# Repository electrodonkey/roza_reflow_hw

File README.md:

# roza_reflow_hw
Reflow controller

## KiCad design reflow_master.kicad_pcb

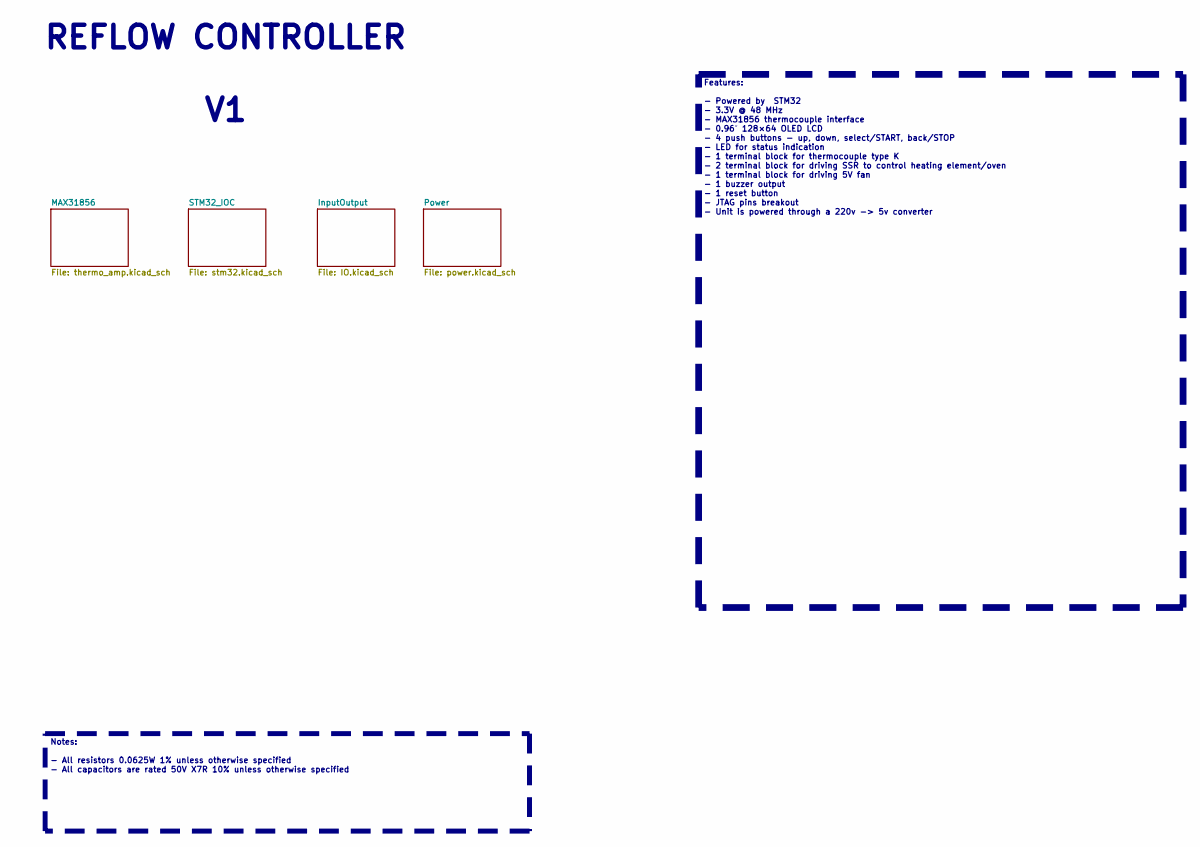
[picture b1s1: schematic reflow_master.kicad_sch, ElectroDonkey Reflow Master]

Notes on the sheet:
Features: - Powered by STM32 - 3.3V @ 48 MHz - MAX31856 thermocouple interface - 0.96″ 128×64 OLED LCD - 4 push buttons - up, down, select/START, back/STOP - LED for status indication - 1 terminal block for thermocouple type K - 2 terminal block for driving SSR to control heating element/oven - 1 t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
Notes: - All resistors 0.0625W 1% unless otherwise specified - All capacitors are rated 50V X7R 10% unless otherwise specified
REFLOW CONTROLLER ${REVISION}

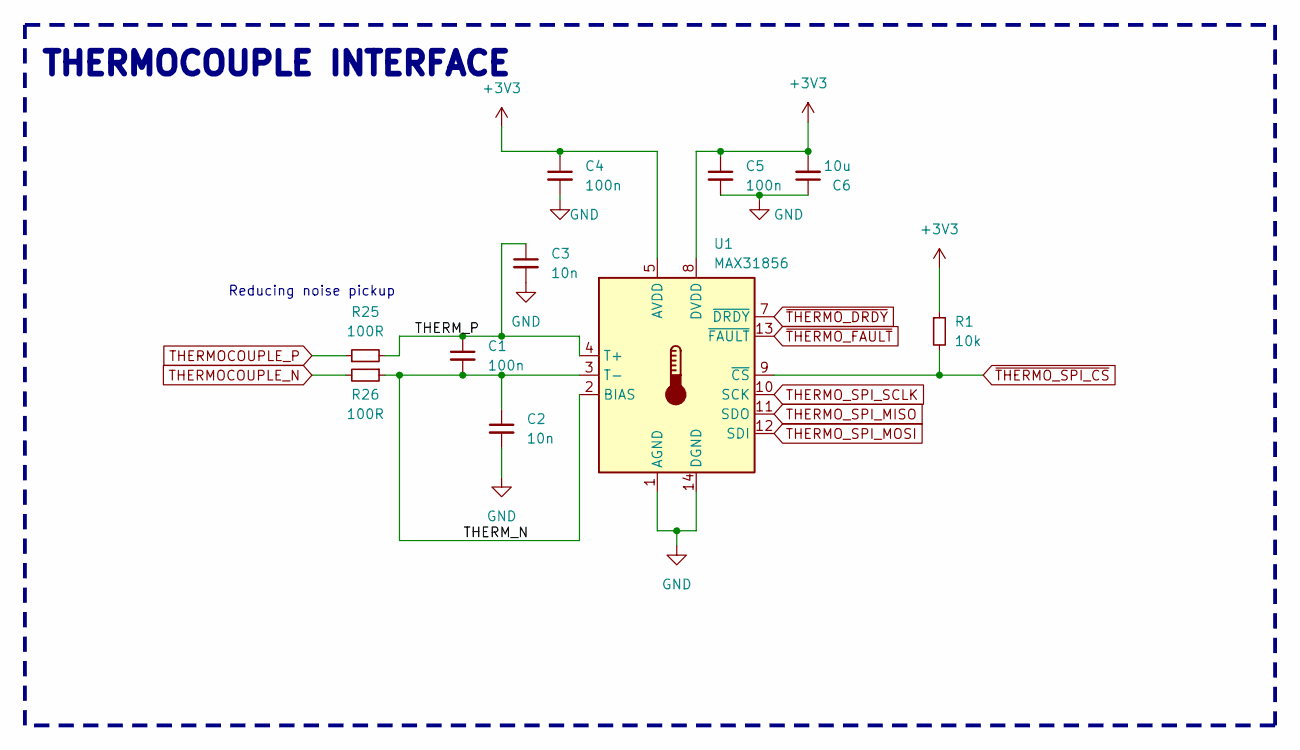
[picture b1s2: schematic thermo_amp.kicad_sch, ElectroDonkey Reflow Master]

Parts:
C1, C4, C5: 100n; C_0603_1608Metric_Pad1.08x0.95mm_HandSolder
C2, C3: 10n; C_0603_1608Metric_Pad1.08x0.95mm_HandSolder
C6: 10u; C_0603_1608Metric_Pad1.08x0.95mm_HandSolder
R1: 10k; R_0603_1608Metric_Pad0.98x0.95mm_HandSolder
R25, R26: 100R; R_0603_1608Metric_Pad0.98x0.95mm_HandSolder
U1: MAX31856; TSSOP-14_4.4x5mm_P0.65mm

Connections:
+3V3: C4.1, C5.1, C6.2, R1.1, U1.5 (AVDD), U1.8 (DVDD); also elsewhere on the board
/MAX31856/THERM_N: C1.2, C2.1, R26.1, U1.2 (BIAS), U1.3 (T-)
/MAX31856/THERM_P: C1.1, C3.1, R25.2, U1.4 (T+)
GND: C2.2, C3.2, C4.2, C5.2, C6.1, U1.1 (AGND), U1.14 (DGND); also elsewhere on the board
THERMOCOUPLE_N: R26.2; also elsewhere on the board
THERMOCOUPLE_P: R25.1; also elsewhere on the board
THERMO_SPI_MISO: U1.11 (SDO); also elsewhere on the board
THERMO_SPI_MOSI: U1.12 (SDI); also elsewhere on the board
THERMO_SPI_SCLK: U1.10 (SCK); also elsewhere on the board
~THERMO_DRDY: U1.7 (~DRDY); also elsewhere on the board
~THERMO_FAULT: U1.13 (~FAULT); also elsewhere on the board
~THERMO_SPI_CS: R1.2, U1.9 (~CS); also elsewhere on the board

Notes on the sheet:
Reducing noise pickup
THERMOCOUPLE INTERFACE

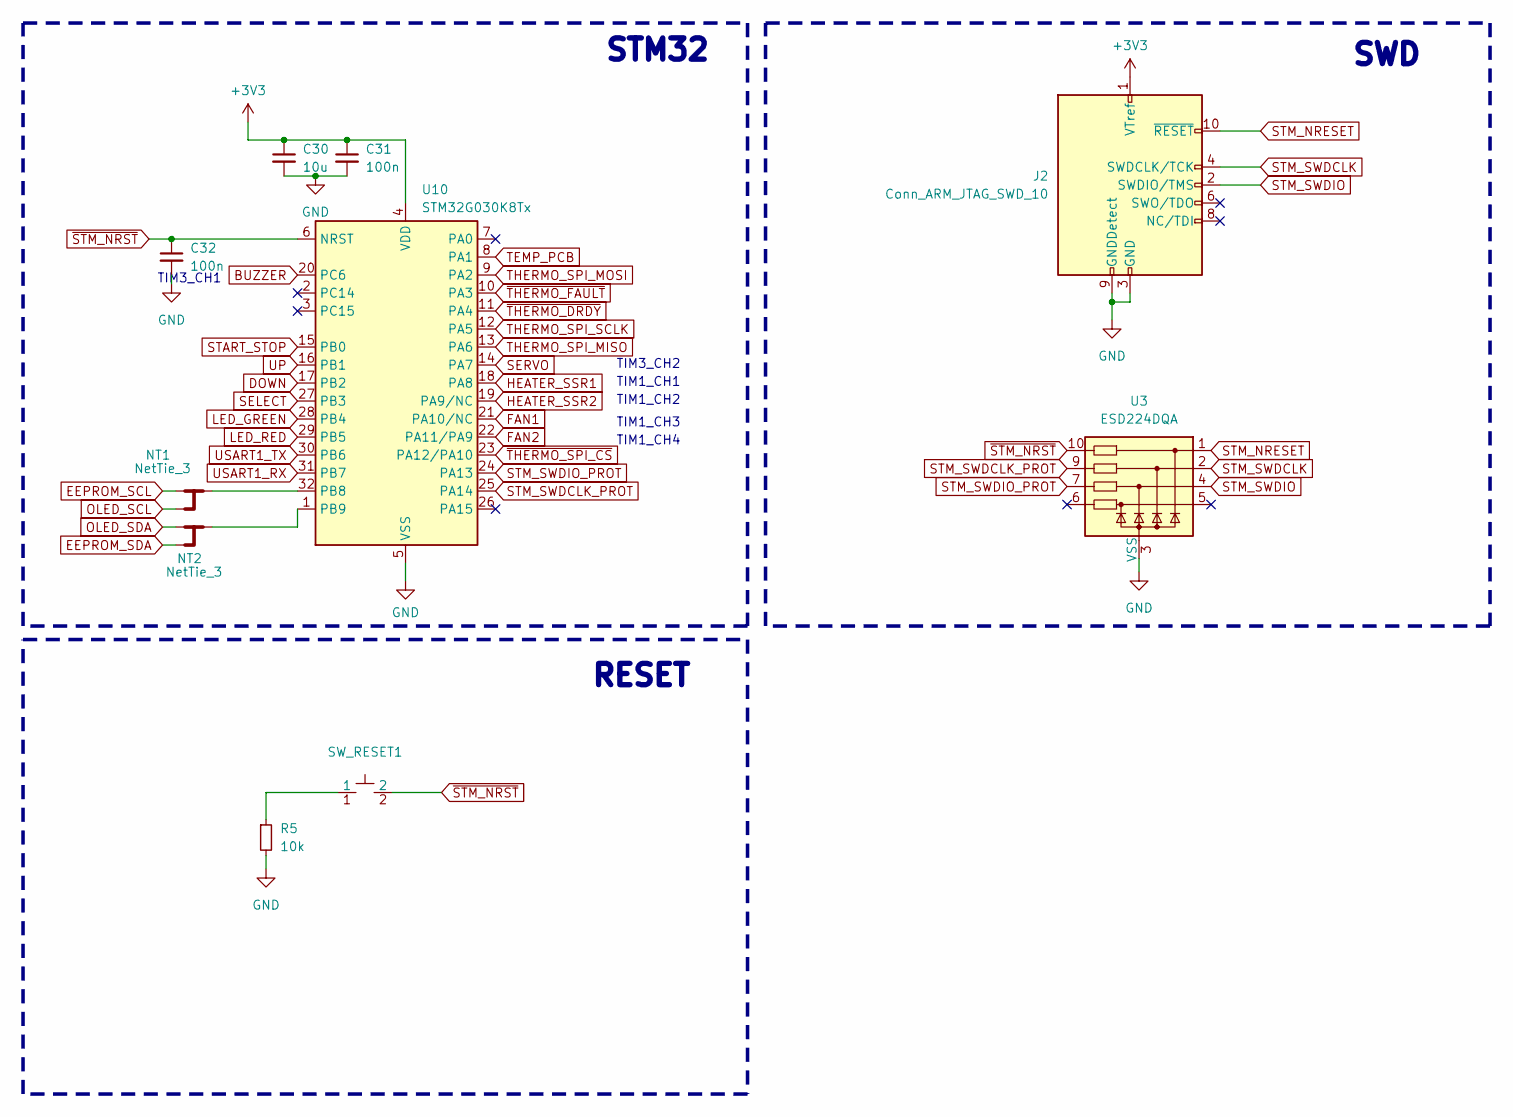
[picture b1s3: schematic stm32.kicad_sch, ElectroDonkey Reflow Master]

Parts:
C30: 10u; C_0603_1608Metric_Pad1.08x0.95mm_HandSolder
C31, C32: 100n; C_0603_1608Metric_Pad1.08x0.95mm_HandSolder
J2: Conn_ARM_JTAG_SWD_10; PinHeader_2x05_P1.27mm_Vertical
NT1, NT2: NetTie_3; NetTie-3_SMD_Pad0.5mm
R5: 10k; R_0603_1608Metric_Pad0.98x0.95mm_HandSolder
SW_RESET1: TL1017AABF160QG
U3: ESD224DQA; Diodes_UDFN-10_1.0x2.5mm_P0.5mm
U10: STM32G030K8Tx; LQFP-32_7x7mm_P0.8mm

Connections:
+3V3: C30.1, C31.1, J2.1 (VTref), U10.4 (VDD); also elsewhere on the board
BUZZER: U10.20 (PC6); also elsewhere on the board
DOWN: U10.17 (PB2); also elsewhere on the board
EEPROM_SCL: NT1.1; also elsewhere on the board
EEPROM_SDA: NT2.3; also elsewhere on the board
FAN1: U10.21 (PA10/NC); also elsewhere on the board
FAN2: U10.22 (PA11/PA9); also elsewhere on the board
GND: C30.2, C31.2, C32.2, J2.3 (GND), J2.5 (GND), J2.9 (GNDDetect), R5.2, U3.3 (VSS), U3.8 (VSS), U10.5 (VSS); also elsewhere on the board
HEATER_SSR1: U10.18 (PA8); also elsewhere on the board
HEATER_SSR2: U10.19 (PA9/NC); also elsewhere on the board
LED_GREEN: U10.28 (PB4); also elsewhere on the board
LED_RED: U10.29 (PB5); also elsewhere on the board
unnamed: R5.1, SW_RESET1.1
unnamed: NT1.2, U10.32 (PB8)
unnamed: NT2.2, U10.1 (PB9)
OLED_SCL: NT1.3; also elsewhere on the board
OLED_SDA: NT2.1; also elsewhere on the board
SELECT: U10.27 (PB3); also elsewhere on the board
SERVO: U10.14 (PA7); also elsewhere on the board
START_STOP: U10.15 (PB0); also elsewhere on the board
STM_NRESET: J2.10 (~RESET), U3.1
STM_SWDCLK: J2.4 (SWDCLK/TCK), U3.2
STM_SWDCLK_PROT: U3.9, U10.25 (PA14)
STM_SWDIO: J2.2 (SWDIO/TMS), U3.4
STM_SWDIO_PROT: U3.7, U10.24 (PA13)
TEMP_PCB: U10.8 (PA1); also elsewhere on the board
THERMO_SPI_MISO: U10.13 (PA6); also elsewhere on the board
THERMO_SPI_MOSI: U10.9 (PA2); also elsewhere on the board
THERMO_SPI_SCLK: U10.12 (PA5); also elsewhere on the board
UP: U10.16 (PB1); also elsewhere on the board
USART1_RX: U10.31 (PB7); also elsewhere on the board
USART1_TX: U10.30 (PB6); also elsewhere on the board
~STM_NRST: C32.1, SW_RESET1.2, U3.10, U10.6 (NRST)
~THERMO_DRDY: U10.11 (PA4); also elsewhere on the board
~THERMO_FAULT: U10.10 (PA3); also elsewhere on the board
~THERMO_SPI_CS: U10.23 (PA12/PA10); also elsewhere on the board

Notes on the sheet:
TIM1_CH2
TIM3_CH1
STM32
RESET
TIM1_CH3
TIM3_CH2
SWD
TIM1_CH4
TIM1_CH1

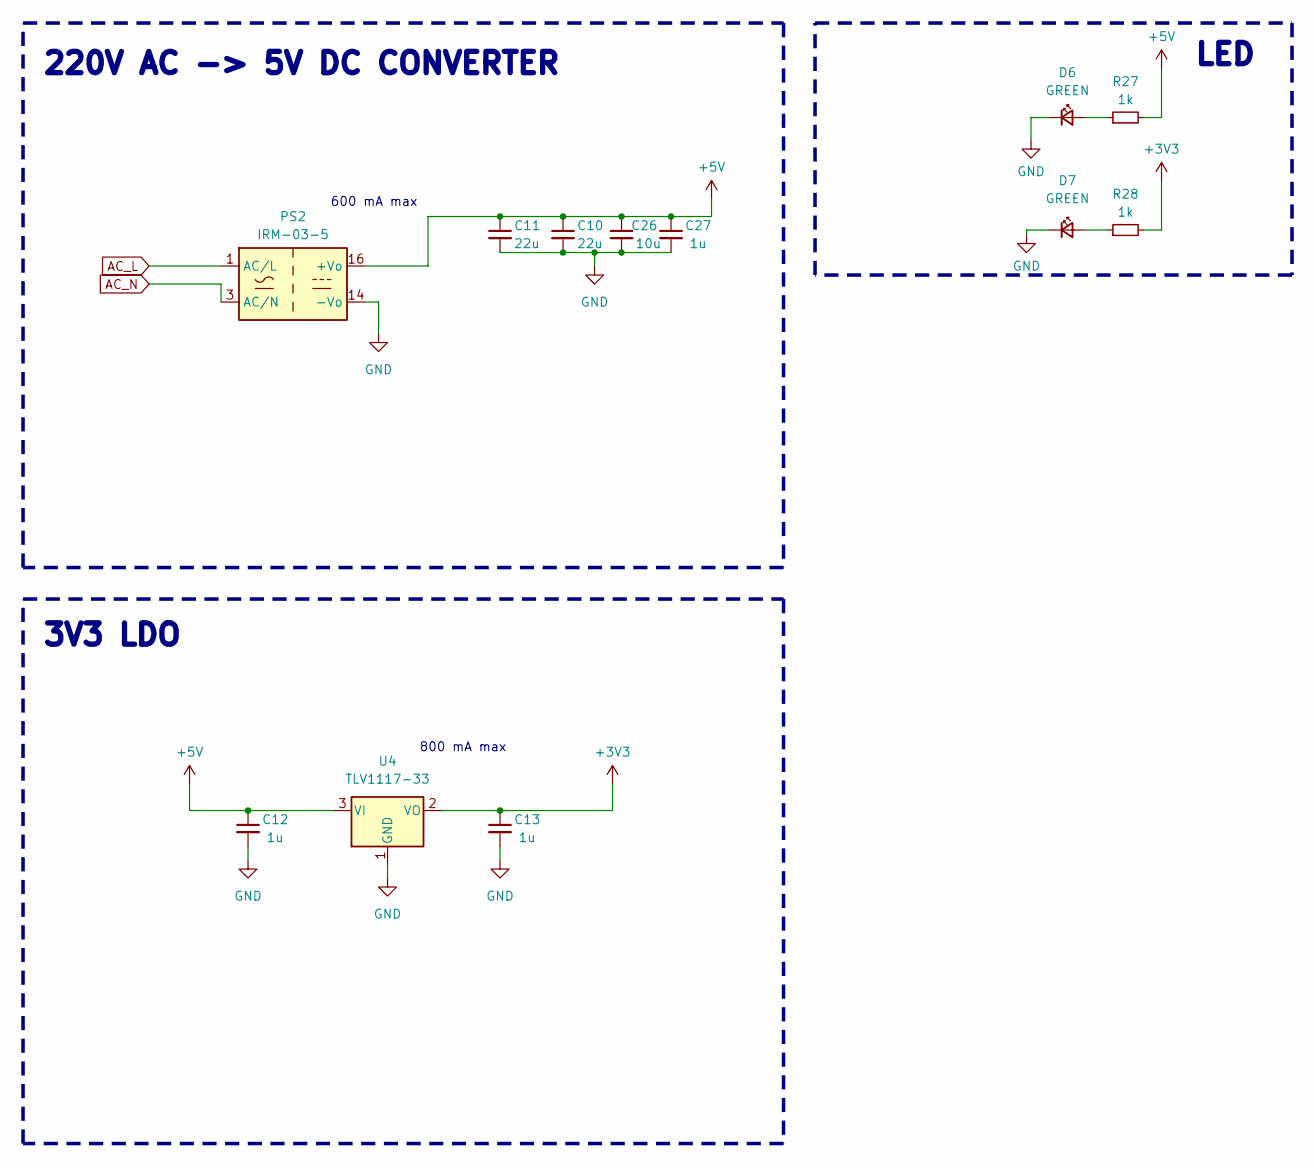
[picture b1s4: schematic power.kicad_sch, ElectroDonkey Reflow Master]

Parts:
C10, C11: 22u; C_1210_3225Metric_Pad1.33x2.70mm_HandSolder
C12, C13, C27: 1u; C_1210_3225Metric_Pad1.33x2.70mm_HandSolder
C26: 10u; C_1210_3225Metric_Pad1.33x2.70mm_HandSolder
D6, D7: GREEN; LED_0603_1608Metric_Pad1.05x0.95mm_HandSolder
PS2: IRM-03-5; Converter_ACDC_MeanWell_IRM-03-xx_THT
R27, R28: 1k; R_0603_1608Metric_Pad0.98x0.95mm_HandSolder
U4: TLV1117-33; SOT-223-3_TabPin2

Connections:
+3V3: C13.1, R28.2, U4.2 (VO); also elsewhere on the board
+5V: C10.1, C11.1, C12.1, C26.1, C27.1, PS2.16 (+Vo), R27.2, U4.3 (VI); also elsewhere on the board
AC_L: PS2.1 (AC/L); also elsewhere on the board
AC_N: PS2.3 (AC/N); also elsewhere on the board
GND: C10.2, C11.2, C12.2, C13.2, C26.2, C27.2, D6.1 (K), D7.1 (K), PS2.14 (-Vo), U4.1 (GND); also elsewhere on the board
unnamed: D6.2 (A), R27.1
unnamed: D7.2 (A), R28.1

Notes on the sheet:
3V3 LDO
220V AC -> 5V DC CONVERTER
LED
600 mA max
800 mA max

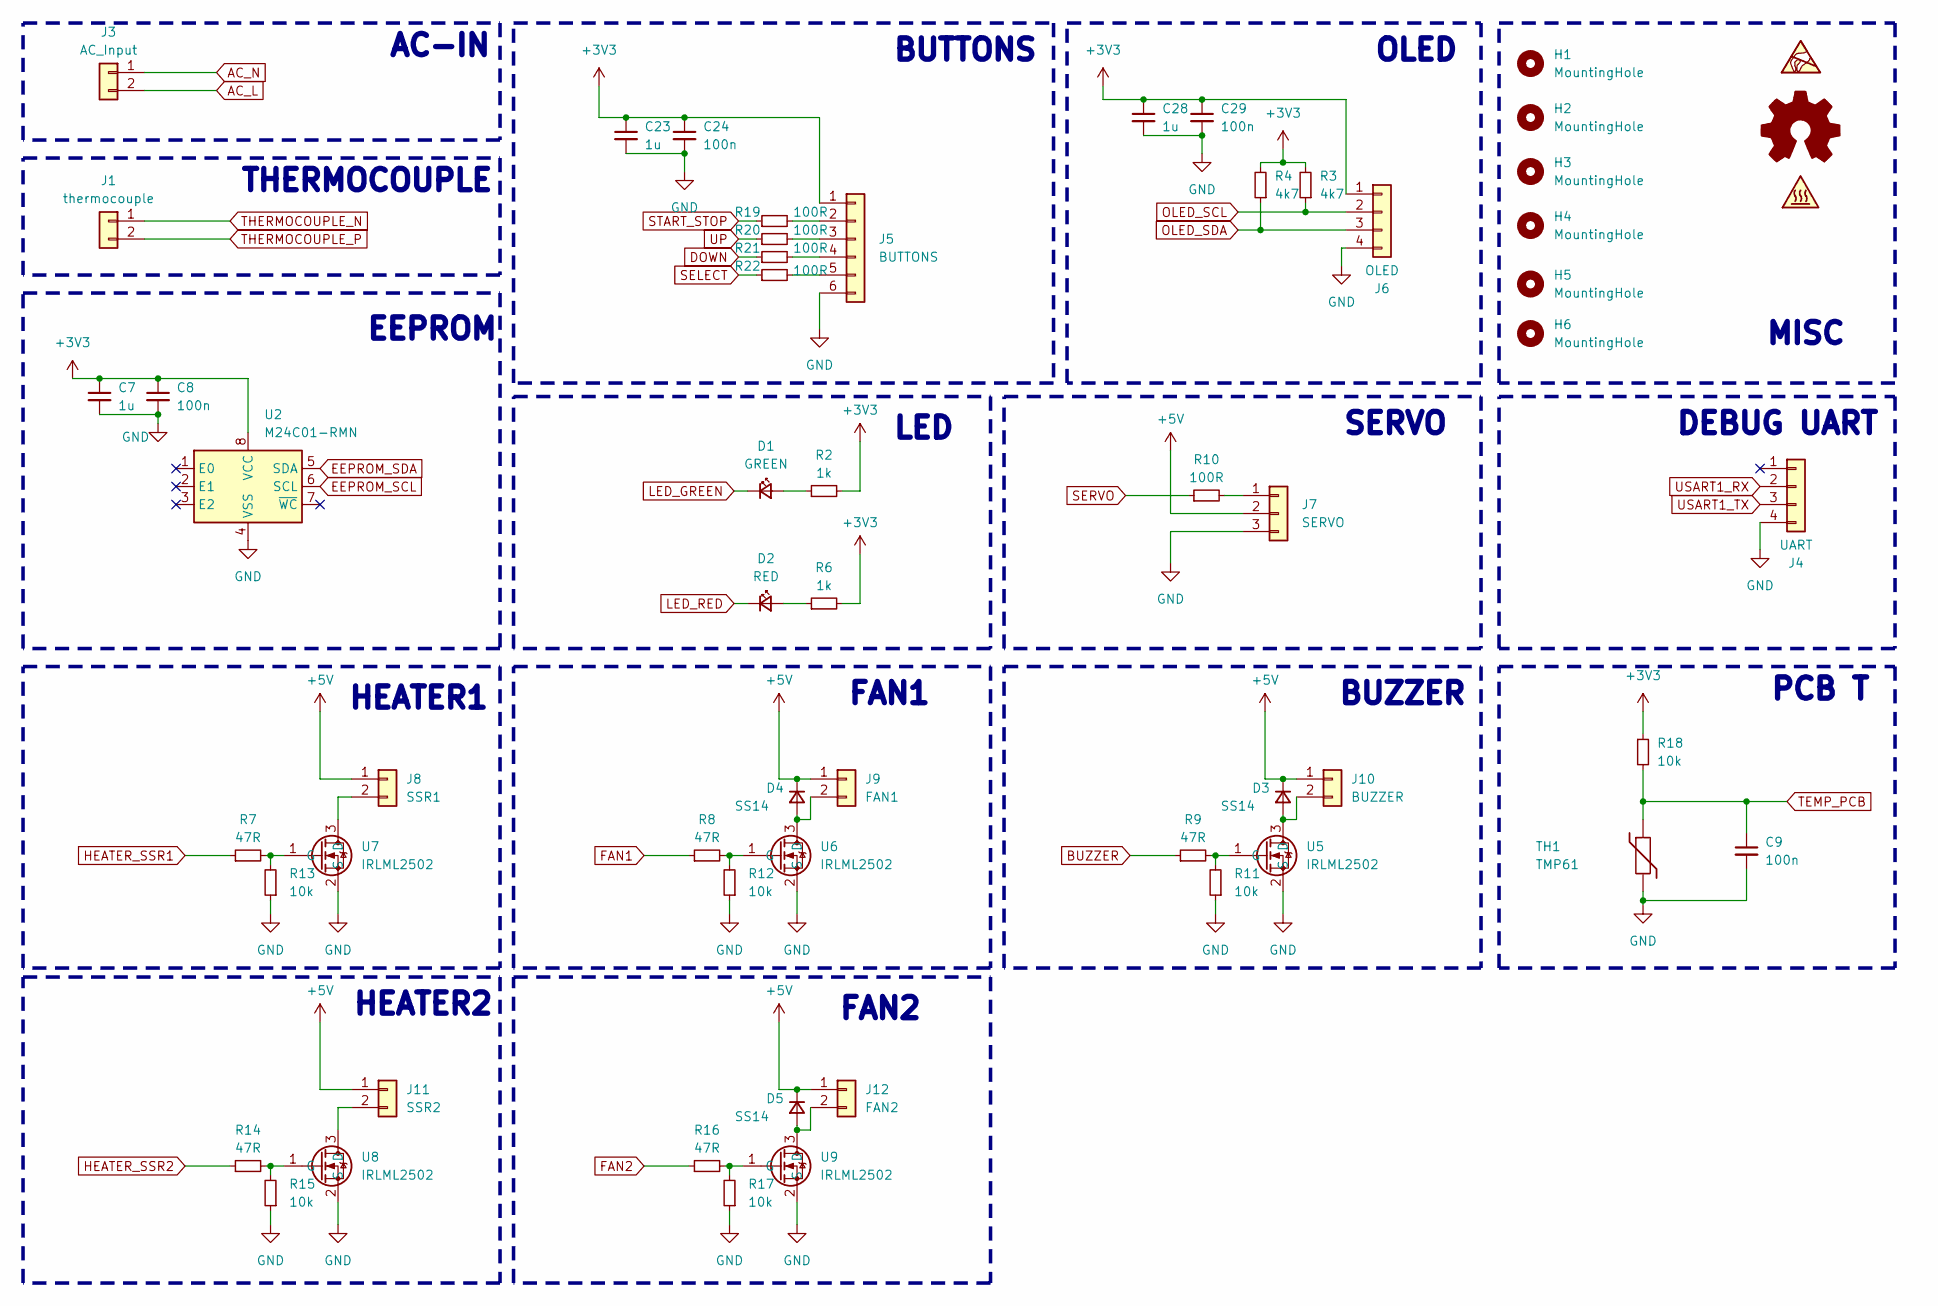
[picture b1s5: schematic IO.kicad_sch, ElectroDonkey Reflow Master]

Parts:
C7, C23, C28: 1u; C_0603_1608Metric_Pad1.08x0.95mm_HandSolder
C8, C9, C24, C29: 100n; C_0603_1608Metric_Pad1.08x0.95mm_HandSolder
D1: GREEN; LED_0603_1608Metric_Pad1.05x0.95mm_HandSolder
D2: RED; LED_0603_1608Metric_Pad1.05x0.95mm_HandSolder
D3, D4, D5: SS14; D_SOD-123
H1, H2, H3, H4, H5, H6: MountingHole; MountingHole_3.2mm_M3
J1: thermocouple; TerminalBlock_Phoenix_MKDS-1,5-2_1x02_P5.00mm_Horizontal
J3: AC_Input; TerminalBlock_Phoenix_MKDS-1,5-2_1x02_P5.00mm_Horizontal
J4: UART; PinHeader_1x04_P2.54mm_Vertical
J5: BUTTONS; Molex_Nano-Fit_105309-xx06_1x06_P2.50mm_Vertical
J6: OLED; Molex_Nano-Fit_105309-xx04_1x04_P2.50mm_Vertical
J7: SERVO; PinHeader_1x03_P2.54mm_Vertical
J8: SSR1; Molex_Nano-Fit_105309-xx02_1x02_P2.50mm_Vertical
J9: FAN1; Molex_Nano-Fit_105309-xx02_1x02_P2.50mm_Vertical
J10: BUZZER; Molex_Nano-Fit_105309-xx02_1x02_P2.50mm_Vertical
J11: SSR2; Molex_Nano-Fit_105309-xx02_1x02_P2.50mm_Vertical
J12: FAN2; Molex_Nano-Fit_105309-xx02_1x02_P2.50mm_Vertical
R2, R6: 1k; R_0603_1608Metric_Pad0.98x0.95mm_HandSolder
R3, R4: 4k7; R_0603_1608Metric_Pad0.98x0.95mm_HandSolder
R7, R8, R9, R14, R16: 47R; R_0603_1608Metric_Pad0.98x0.95mm_HandSolder
R10, R19, R20, R21, R22: 100R; R_0603_1608Metric_Pad0.98x0.95mm_HandSolder
R11, R12, R13, R15, R17, R18: 10k; R_0603_1608Metric_Pad0.98x0.95mm_HandSolder
TH1: TMP61; Texas_DPY0002A_0.6x1mm_P0.65mm
U2: M24C01-RMN; SOIC-8_3.9x4.9mm_P1.27mm
U5, U6, U7, U8, U9: IRLML2502; SOT-23

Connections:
+3V3: C7.1, C8.1, C23.1, C24.1, C28.1, C29.1, J5.1, J6.1, R2.2, R3.2, R4.2, R6.2, R18.1, U2.8 (VCC); also elsewhere on the board
+5V: D3.1 (K), D4.1 (K), D5.1 (K), J7.2, J8.1, J9.1, J10.1, J11.1, J12.1; also elsewhere on the board
AC_L: J3.2; also elsewhere on the board
AC_N: J3.1; also elsewhere on the board
BUZZER: R9.1; also elsewhere on the board
DOWN: R21.1; also elsewhere on the board
EEPROM_SCL: U2.6 (SCL); also elsewhere on the board
EEPROM_SDA: U2.5 (SDA); also elsewhere on the board
FAN1: R8.1; also elsewhere on the board
FAN2: R16.1; also elsewhere on the board
GND: C7.2, C8.2, C9.2, C23.2, C24.2, C28.2, C29.2, J4.4, J5.6, J6.4, J7.3, R11.1, R12.1, R13.1, R15.1, R17.1, TH1.2, U2.4 (VSS), U5.2 (S), U6.2 (S), U7.2 (S), U8.2 (S), U9.2 (S); also elsewhere on the board
HEATER_SSR1: R7.1; also elsewhere on the board
HEATER_SSR2: R14.1; also elsewhere on the board
LED_GREEN: D1.1 (K); also elsewhere on the board
LED_RED: D2.1 (K); also elsewhere on the board
unnamed: D1.2 (A), R2.1
unnamed: D2.2 (A), R6.1
unnamed: D3.2 (A), J10.2, U5.3 (D)
unnamed: D4.2 (A), J9.2, U6.3 (D)
unnamed: D5.2 (A), J12.2, U9.3 (D)
unnamed: J5.2, R19.2
unnamed: J5.3, R20.2
unnamed: J5.4, R21.2
unnamed: J5.5, R22.2
unnamed: J7.1, R10.2
unnamed: J8.2, U7.3 (D)
unnamed: J11.2, U8.3 (D)
unnamed: R9.2, R11.2, U5.1 (G)
unnamed: R8.2, R12.2, U6.1 (G)
unnamed: R7.2, R13.2, U7.1 (G)
unnamed: R14.2, R15.2, U8.1 (G)
unnamed: R16.2, R17.2, U9.1 (G)
OLED_SCL: J6.2, R3.1; also elsewhere on the board
OLED_SDA: J6.3, R4.1; also elsewhere on the board
SELECT: R22.1; also elsewhere on the board
SERVO: R10.1; also elsewhere on the board
START_STOP: R19.1; also elsewhere on the board
TEMP_PCB: C9.1, R18.2, TH1.1; also elsewhere on the board
THERMOCOUPLE_N: J1.1; also elsewhere on the board
THERMOCOUPLE_P: J1.2; also elsewhere on the board
UP: R20.1; also elsewhere on the board
USART1_RX: J4.2; also elsewhere on the board
USART1_TX: J4.3; also elsewhere on the board

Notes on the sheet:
HEATER2
OLED
BUTTONS
FAN2
AC-IN
EEPROM
BUZZER
THERMOCOUPLE
MISC
LED
HEATER1
PCB T
SERVO
FAN1
DEBUG UART

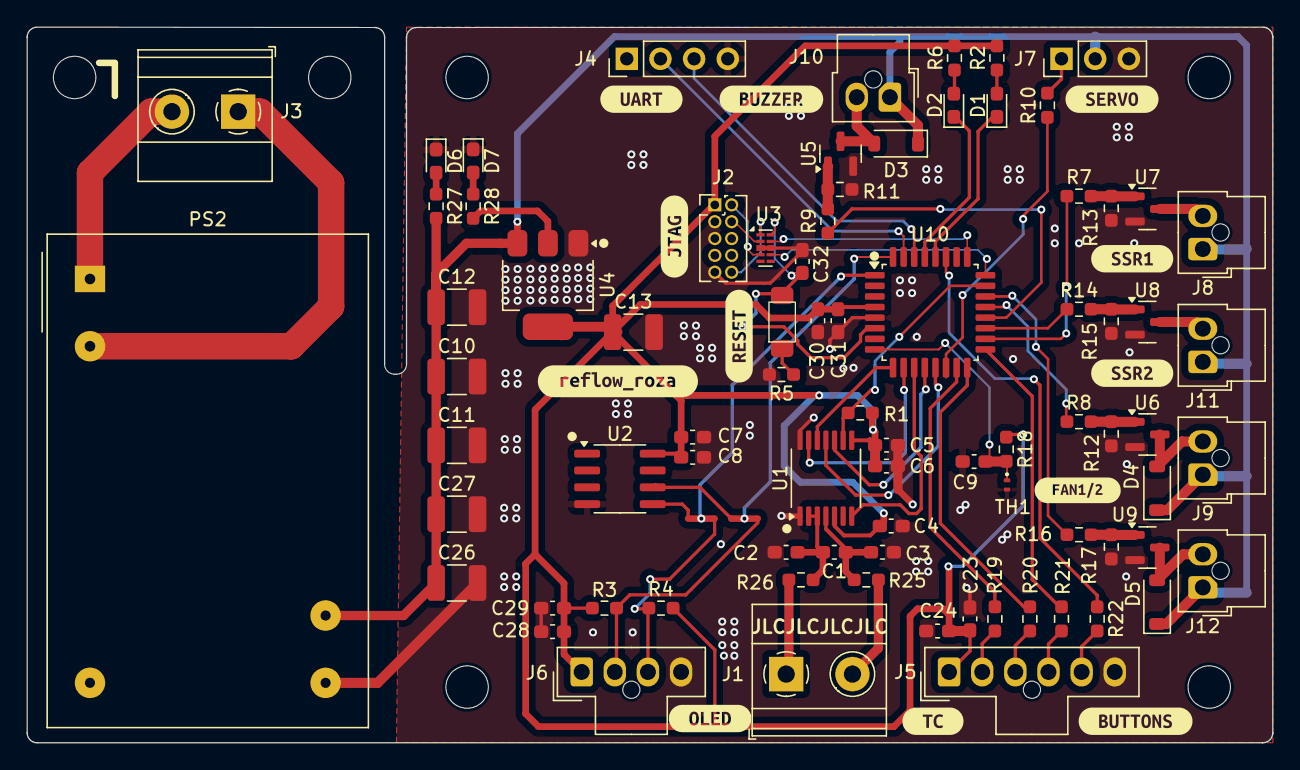
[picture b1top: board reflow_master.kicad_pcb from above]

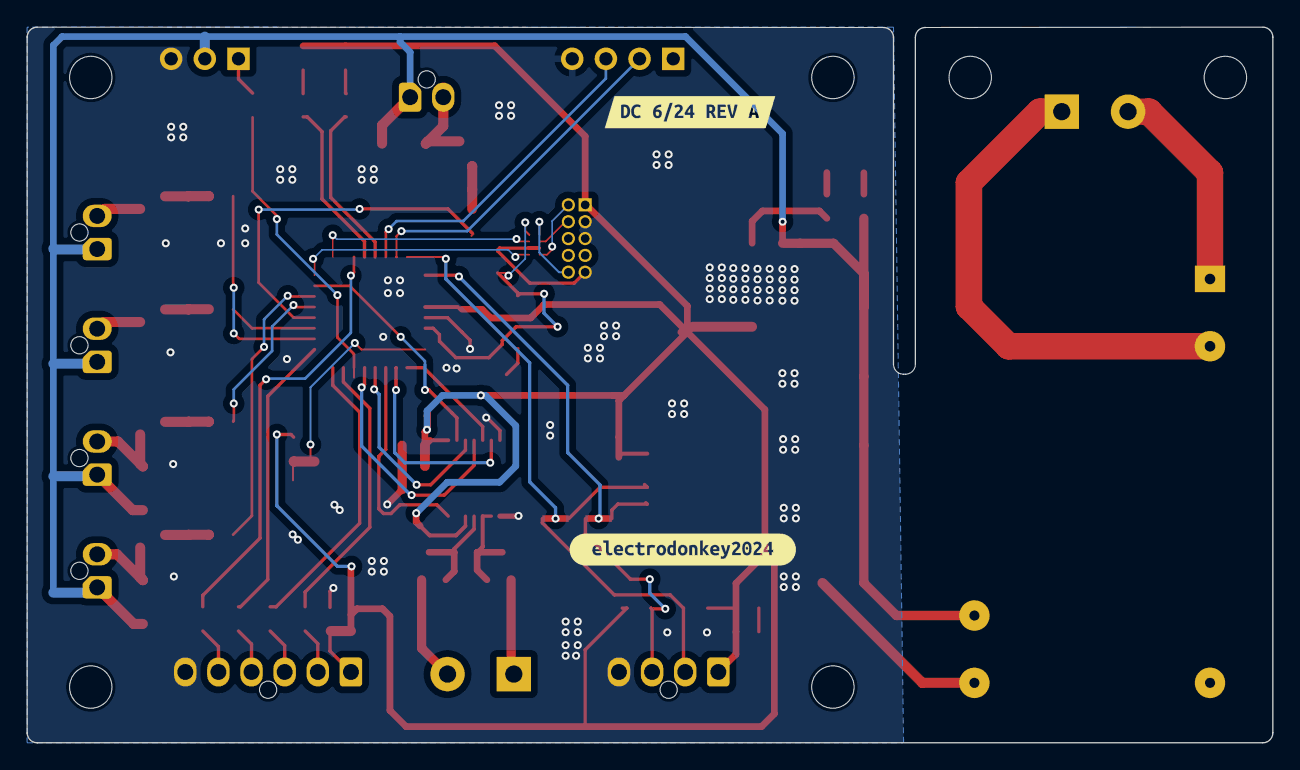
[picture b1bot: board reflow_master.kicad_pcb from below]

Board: 2 copper layers, 94.0 x 54.0 mm, 102 parts (2 on the bottom side), 62 nets.

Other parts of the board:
kibuzzard-667C6A5B: G***; kibuzzard-667C6A5B
kibuzzard-667C6A86: G***; kibuzzard-667C6A86
kibuzzard-667C6AA2: G***; kibuzzard-667C6AA2
kibuzzard-667C6CD5: G***; kibuzzard-667C6CD5
kibuzzard-667C6CE8: G***; kibuzzard-667C6CE8
kibuzzard-667C6E0B: G***; kibuzzard-667C6E0B
kibuzzard-667C6E5A: G***; kibuzzard-667C6E5A
kibuzzard-667C69AB: G***; kibuzzard-667C69AB
kibuzzard-667C69F0: G***; kibuzzard-667C69F0
kibuzzard-667C69F9: G***; kibuzzard-667C69F9
kibuzzard-667C6983: G***; kibuzzard-667C6983
kibuzzard-667C6993: G***; kibuzzard-667C6993
kibuzzard-667E6FEF: G***; kibuzzard-667E6FEF
kibuzzard-667F04CE: G***; kibuzzard-667F04CE

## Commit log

2024-12-30 Add other stuff to .gitignore
2024-12-30 Add initial produced files as of 30/12/2024
2025-01-08 Add reference for enclosure design

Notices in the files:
IO.kicad_sch:
CC-BY-SA 4.0
